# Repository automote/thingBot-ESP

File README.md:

# thingBot-ESP

The thingBot-ESP is based on Espressif ESP8266EX Wi-Fi SoC (System on Chip), featuring a Tensilica L106 32-bit micro controller running at 80 MHz. Features include:

 * 802.11 b/g/n protocol
 * Wi-Fi Direct (P2P), soft-AP
 * Integrated TCP/IP protocol stack
 * Wake up and transmit packets in < 2ms
 * Power down leakage current of < 10uA
 * STBC, 1x1 MIMO, 2x1 MIMO
 
## Platform Features

 * [XBee Compatible](https://www.sparkfun.com/datasheets/Wireless/Zigbee/XBee-Dimensional.pdf)
 * Compatible with Arduino IDE
 * 3.3V Vin
 * UART, SPI, I2C
 * On-board RESET
 
## Maintainers

The thingBot-SubGHz is maintained by thingTronics Innovations.

Main contributor:
 * Lovelesh Patel @<lovelesh.patel@thingtronics.com>
 * Poornima Nagesh @<poornima.nagesh@thingtronics.com>

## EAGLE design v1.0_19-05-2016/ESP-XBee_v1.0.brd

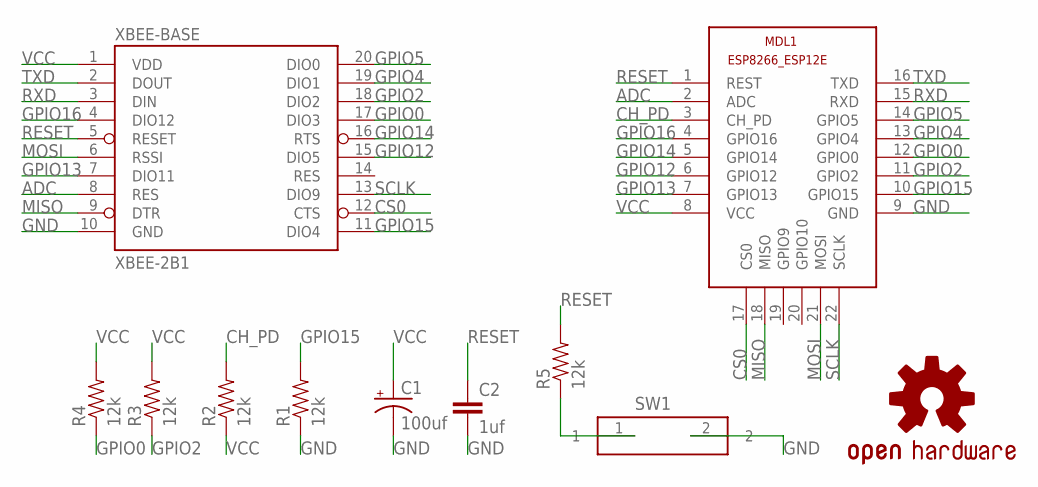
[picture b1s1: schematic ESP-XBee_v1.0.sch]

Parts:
C1: 100uf; EIA3216-KIT
C2: 1uf; 0805
LOGO3: OSHW-LOGOS; OSHW-LOGO-S
MDL1: ESP8266-12EESP8266-ESP12E; ESP8266-ESP12E
R1, R2, R3, R4, R5: 12k; 0805
SW1: 434111043826
XBEE-BASE: XBEE-2B1; XBEE-1

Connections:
ADC: MDL1.2 (ADC), XBEE-BASE.8 (RES)
CH_PD: MDL1.3 (CH_PD), R2.2
CS0: MDL1.17 (CS0), XBEE-BASE.12 (CTS)
GND: C1.C (-), C2.2, MDL1.9 (GND), R1.1, SW1.2, XBEE-BASE.10 (GND)
GPIO0: MDL1.12 (GPIO0), R4.1, XBEE-BASE.17 (DIO3)
GPIO2: MDL1.11 (GPIO2), R3.1, XBEE-BASE.18 (DIO2)
GPIO4: MDL1.13 (GPIO4), XBEE-BASE.19 (DIO1)
GPIO5: MDL1.14 (GPIO5), XBEE-BASE.20 (DIO0)
GPIO12: MDL1.6 (GPIO12), XBEE-BASE.15 (DIO5)
GPIO13: MDL1.7 (GPIO13), XBEE-BASE.7 (DIO11)
GPIO14: MDL1.5 (GPIO14), XBEE-BASE.16 (RTS)
GPIO15: MDL1.10 (GPIO15), R1.2, XBEE-BASE.11 (DIO4)
GPIO16: MDL1.4 (GPIO16), XBEE-BASE.4 (DIO12)
MISO: MDL1.18 (MISO), XBEE-BASE.9 (DTR)
MOSI: MDL1.21 (MOSI), XBEE-BASE.6 (RSSI)
unnamed: R5.1, SW1.1
RESET: C2.1, MDL1.1 (REST), R5.2, XBEE-BASE.5 (RESET)
RXD: MDL1.15 (RXD), XBEE-BASE.3 (DIN)
SCLK: MDL1.22 (SCLK), XBEE-BASE.13 (DIO9)
TXD: MDL1.16 (TXD), XBEE-BASE.2 (DOUT)
VCC: C1.A (+), MDL1.8 (VCC), R2.1, R3.2, R4.2, XBEE-BASE.1 (VDD)

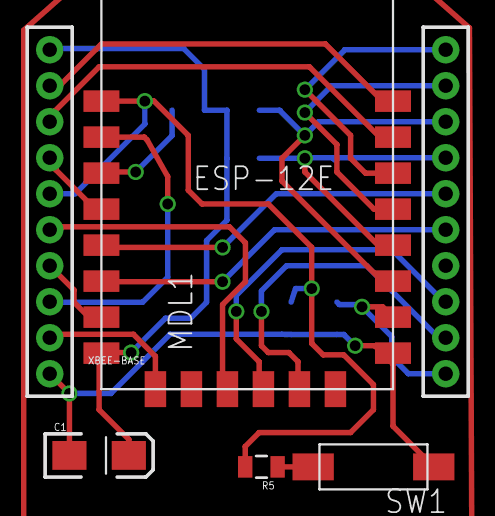
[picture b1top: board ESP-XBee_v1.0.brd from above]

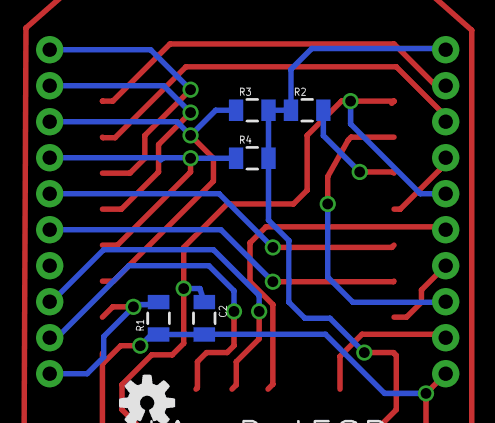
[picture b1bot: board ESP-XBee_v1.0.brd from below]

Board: 2 copper layers, 11 parts (6 on the bottom side), 21 nets.

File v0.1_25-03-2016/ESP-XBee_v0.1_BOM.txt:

Partlist exported from P:/PCB Design/ESP-XBee/ESP-XBee.sch at 25-03-2016 20:31

Part      Value        Device                    Package        Description                                             
C1        100uf        CAP_POL1206-KIT           EIA3216-KIT    Capacitor Polarized                                     
C2        1uf          CAP0805                   0805           Capacitor                                               
LOGO3     OSHW-LOGOS   OSHW-LOGOS                OSHW-LOGO-S    Open Source Hardware Logo                               
MDL1                   ESP8266-12EESP8266-ESP12E ESP8266-ESP12E ESP8266-12E with additional I/O and GPIO04/05 corrected 
R1        12k          RESISTOR0805-RES          0805           Resistor                                                
R2        12k          RESISTOR0805-RES          0805           Resistor                                                
R3        12k          RESISTOR0805-RES          0805           Resistor                                                
R4        12k          RESISTOR0805-RES          0805           Resistor                                                
R5        12k          RESISTOR0805-RES          0805           Resistor                                                
SW1       434111043826 434111043826              434111043826   WS-TRS-6x3.5 mm SMD Tact Switch, 2 pins                 
XBEE-BASE XBEE-2B1     XBEE-2B1                  XBEE-1         Xbee module footprints

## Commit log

2016-03-25 :tada: Added .gitattributes & .gitignore files
2016-03-25 initial routing done.
    Initial routing complete v0.1 ready
2016-03-25 seeedstudio GERBER generated
2016-03-25 Revert "seeedstudio GERBER generated"
    This reverts commit 3978db2b9afe7cefcf6061ea9ca2f2ffcfdcaa63.
2016-03-25 final GERBER generated
2016-03-25 v0.1 ready for fab
2016-03-25 removed zip
2016-03-25 ignoring all zip and rar files
2016-03-26 added board pdf
2016-05-19 segregated the hardware version into different folders
2017-01-28 made README similar to other thingBots
2017-01-28 minoe changes to README
2017-02-08 done changes according to new thingbot
2017-02-08 minor changes
2017-02-09 schematic verified
2017-02-09 updated .gitignore for KiCad
2017-02-09 added poornima as contributor

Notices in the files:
parts and their libraries:
SparkFun-Capacitors: Licensing: Creative Commons ShareAlike 4.0 International - https://creativecommons.org/licenses/by-sa/4.0
Switches_rev16a: Copyright: Würth Elektronik
